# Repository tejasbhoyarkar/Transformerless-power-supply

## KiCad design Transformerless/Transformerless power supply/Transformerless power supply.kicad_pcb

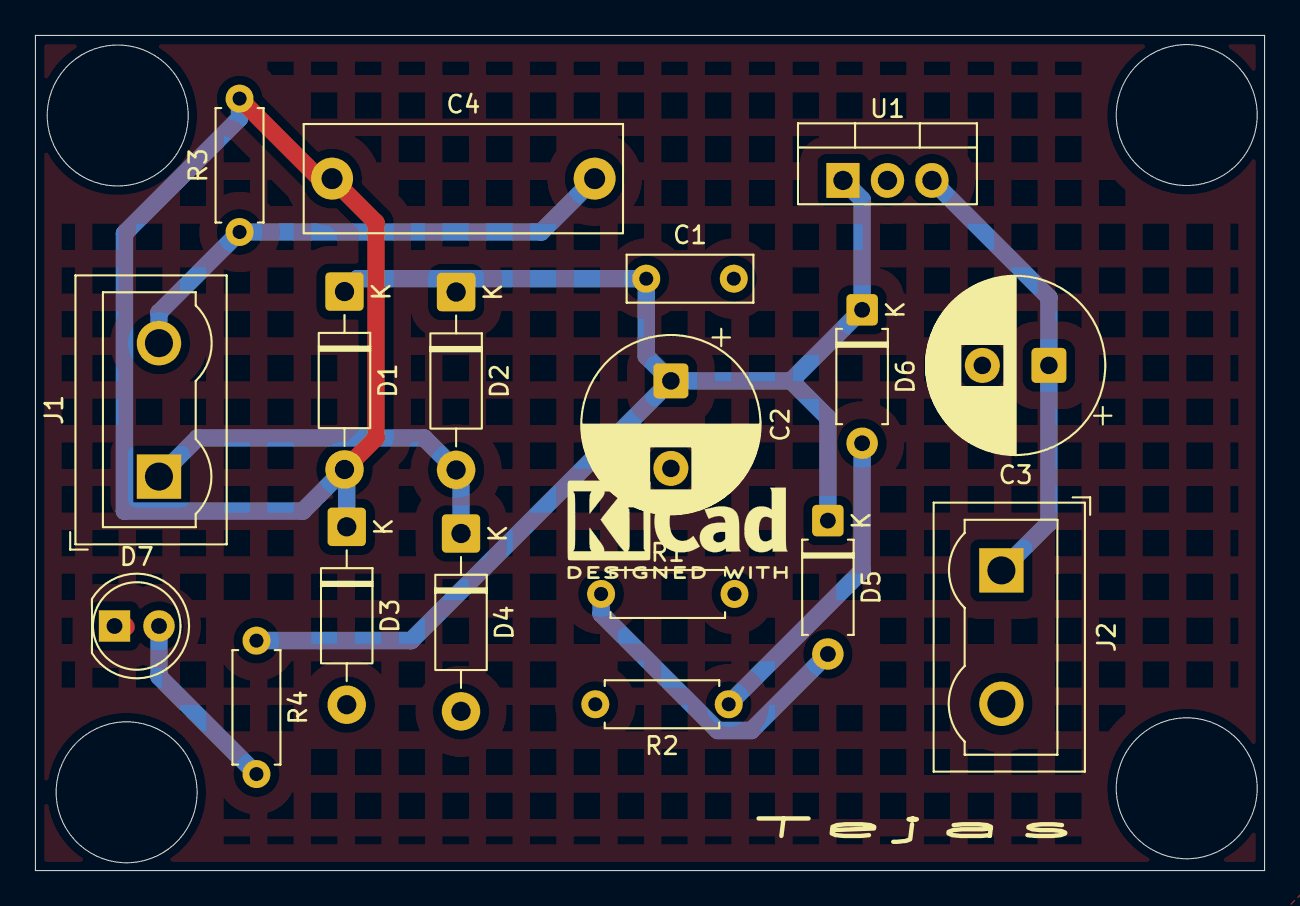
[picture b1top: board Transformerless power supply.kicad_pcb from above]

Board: 2 copper layers, 70.2 x 47.7 mm, 18 parts (0 on the bottom side), 9 nets.

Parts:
C1: 0.1uF; C_Disc_D7.0mm_W2.5mm_P5.00mm
C2: 1000uF; CP_Radial_D10.0mm_P5.00mm
C3: 470uF; CP_Radial_D10.0mm_P3.80mm
C4: 225k/2.2uF; C_Rect_L18.0mm_W6.0mm_P15.00mm_FKS3_FKP3
D1, D2, D3, D4: 1N4007; D_DO-41_SOD81_P10.16mm_Horizontal
D5, D6: D_Zener; D_A-405_P7.62mm_Horizontal
D7: LED; LED_D5.0mm
J1, J2: Screw_Terminal_01x02; TerminalBlock_Wuerth_691311400102_P7.62mm
R1, R2: 20k; R_Axial_DIN0207_L6.3mm_D2.5mm_P7.62mm_Horizontal
R3: 1M; R_Axial_DIN0207_L6.3mm_D2.5mm_P7.62mm_Horizontal
R4: 2.2k; R_Axial_DIN0207_L6.3mm_D2.5mm_P7.62mm_Horizontal
U1: LM7805_TO220; TO-220-3_Vertical

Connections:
GND: C1.2, C2.2, C3.2, D3.2 (A), D4.2 (A), D7.1 (K), J2.2, R1.2, R2.2, U1.2 (GND)
unnamed: C4.1, D1.2 (A), D3.1 (K), R3.2
unnamed: C1.1, C2.1, D1.1 (K), D2.1 (K), D5.1 (K), D6.1 (K), R4.1, U1.1 (VI)
unnamed: D2.2 (A), D4.1 (K), J1.1
unnamed: D5.2 (A), R1.1
unnamed: D6.2 (A), R2.1
unnamed: D7.2 (A), R4.2
unnamed: C4.2, J1.2, R3.1
unnamed: C3.1, J2.1, U1.3 (VO)
